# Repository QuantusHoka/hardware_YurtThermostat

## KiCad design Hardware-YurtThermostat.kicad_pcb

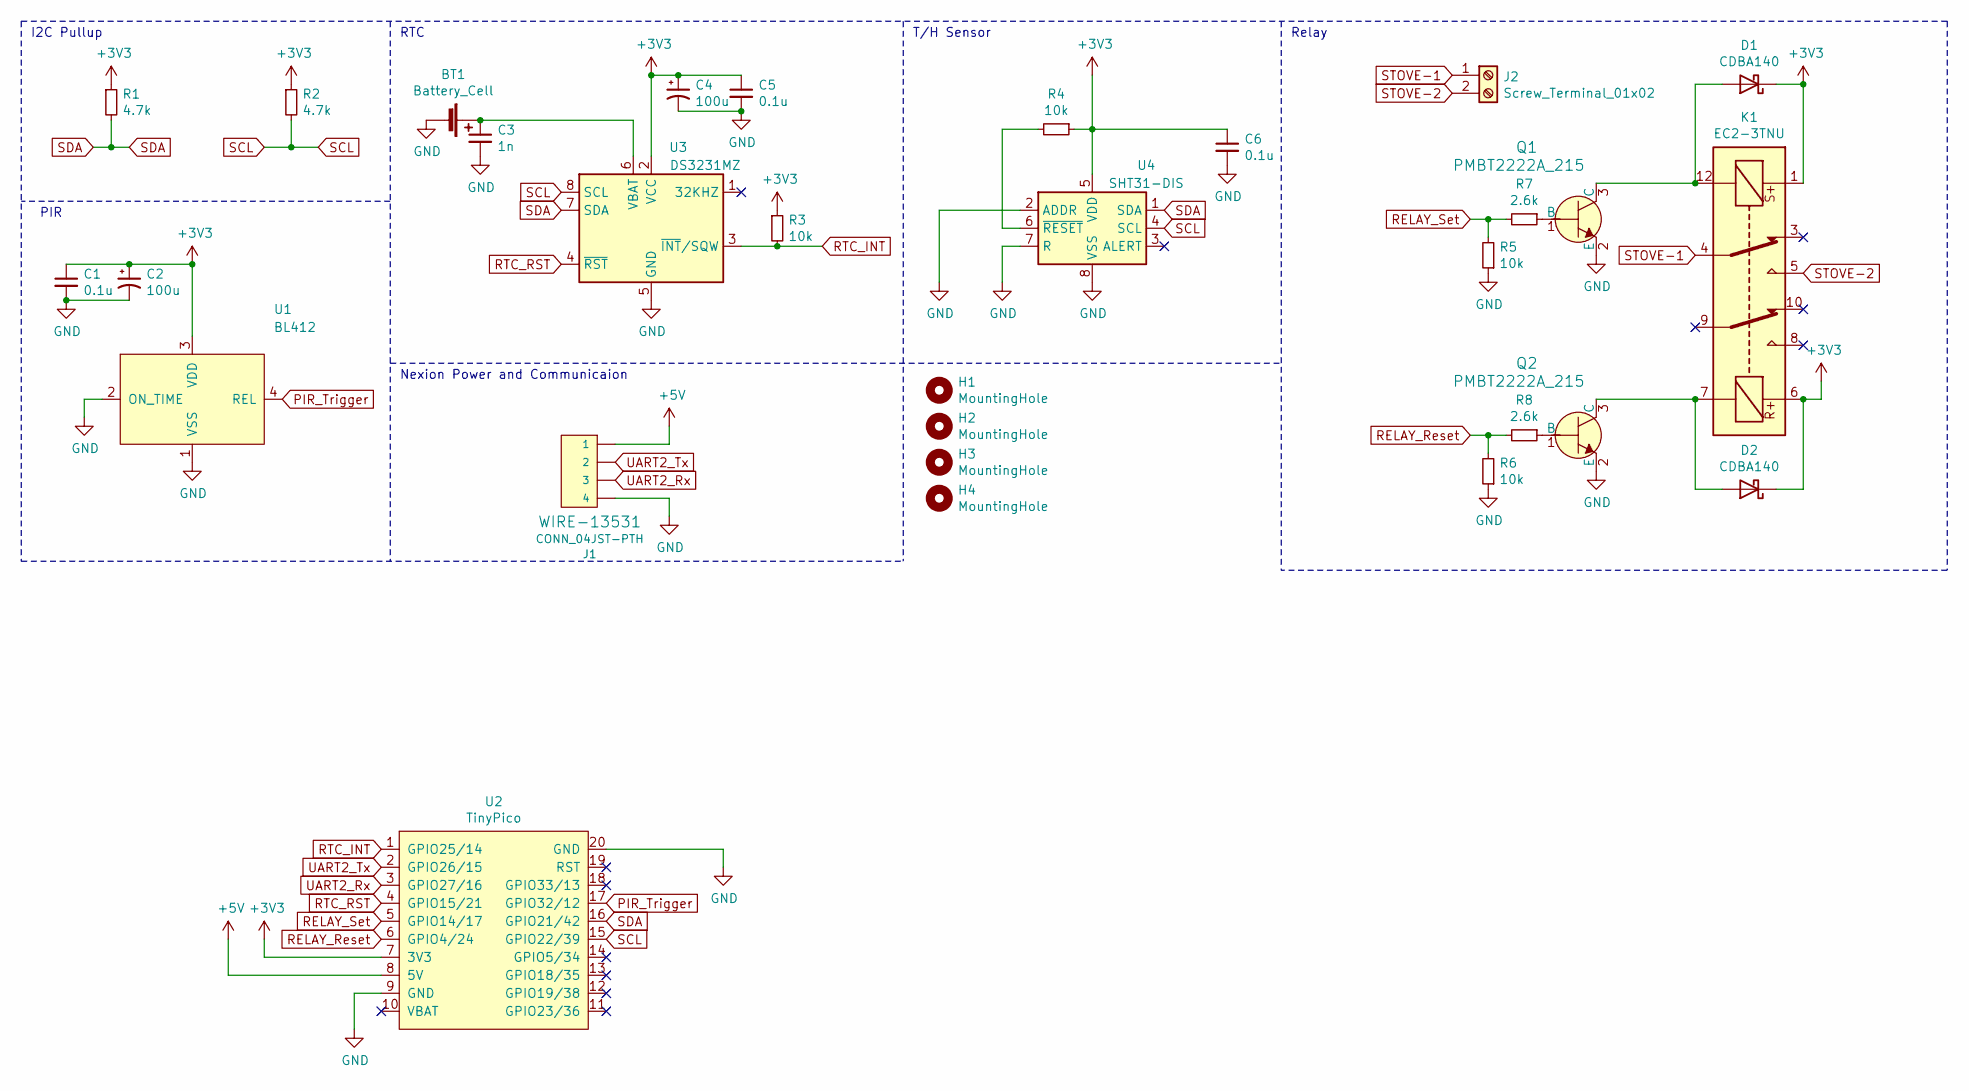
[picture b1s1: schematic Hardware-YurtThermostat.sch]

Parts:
BT1: Battery_Cell; BatteryHolder_Keystone_1060_1x2032
C1, C5, C6: 0.1u; C_0805_2012Metric_Pad1.18x1.45mm_HandSolder
C2, C4: 100u; CP_Elec_5x5.4
C3: 1n; C_0805_2012Metric_Pad1.18x1.45mm_HandSolder
D1, D2: CDBA140; D_SMA
H1, H2, H3, H4: MountingHole; MountingHole_3mm_Pad_TopBottom
J1: CONN_04JST-PTH; JST-4-PTH
J2: Screw_Terminal_01x02; Term_Block_1x2_P5mm
K1: EC2-3TNU; Relay_DPDT_Kemet_EC2_DoubleCoil
Q1, Q2: PMBT2222A_215; SOT-23-3; MPN PMBT2222A,215; Digi-Key_PN 1727-2956-1-ND
R1, R2: 4.7k; R_0805_2012Metric_Pad1.20x1.40mm_HandSolder
R3, R4, R5, R6: 10k; R_0805_2012Metric_Pad1.20x1.40mm_HandSolder
R7, R8: 2.6k; R_0805_2012Metric_Pad1.20x1.40mm_HandSolder
U1: BL412
U2: TinyPico
U3: DS3231MZ; SOIC-8_3.9x4.9mm_P1.27mm
U4: SHT31-DIS; Sensirion_DFN-8-1EP_2.5x2.5mm_P0.5mm_EP1.1x1.7mm

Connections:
+3V3: C1.1, C2.1, C4.1, C5.1, C6.1, D1.1 (K), D2.1 (K), K1.1, K1.6, R1.1, R2.1, R3.1, R4.1, U1.3 (VDD), U2.7 (3V3), U3.2 (VCC), U4.5 (VDD)
+5V: J1.1, U2.8 (5V)
GND: BT1.2 (-), C1.2, C2.2, C3.2, C4.2, C5.2, C6.2, J1.4, Q1.2 (E), Q2.2 (E), R5.1, R6.1, U1.1 (VSS), U1.2 (ON_TIME), U2.9 (GND), U2.20 (GND), U3.5 (GND), U4.2 (ADDR), U4.7 (R), U4.8 (VSS), U4.9 (VSS)
unnamed: BT1.1 (+), C3.1, U3.6 (VBAT)
unnamed: D1.2 (A), K1.12, Q1.3 (C)
unnamed: D2.2 (A), K1.7, Q2.3 (C)
unnamed: Q1.1 (B), R7.1
unnamed: Q2.1 (B), R8.1
unnamed: R4.2, U4.6 (~RESET)
PIR_Trigger: U1.4 (REL), U2.17 (GPIO32/12)
RELAY_Reset: R6.2, R8.2, U2.6 (GPIO4/24)
RELAY_Set: R5.2, R7.2, U2.5 (GPIO14/17)
RTC_INT: R3.2, U2.1 (GPIO25/14), U3.3 (~INT~/SQW)
RTC_RST: U2.4 (GPIO15/21), U3.4 (~RST)
SCL: R2.2, U2.15 (GPIO22/39), U3.8 (SCL), U4.4 (SCL)
SDA: R1.2, U2.16 (GPIO21/42), U3.7 (SDA), U4.1 (SDA)
STOVE-1: J2.1, K1.4
STOVE-2: J2.2, K1.5
UART2_Rx: J1.3, U2.3 (GPIO27/16)
UART2_Tx: J1.2, U2.2 (GPIO26/15)

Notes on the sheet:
I2C Pullup
PIR
RTC
Nexion Power and Communicaion
T/H Sensor
Relay

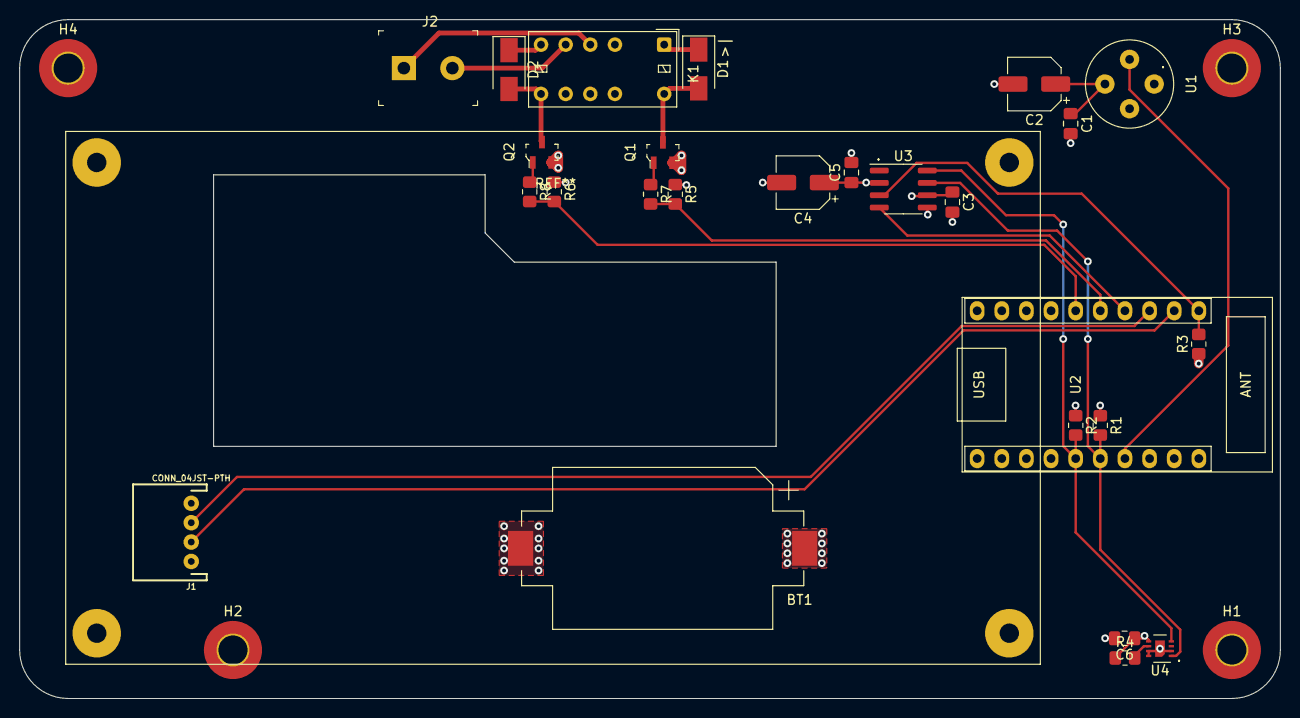
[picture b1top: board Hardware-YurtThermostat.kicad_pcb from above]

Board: 4 copper layers, 130.0 x 70.0 mm, 30 parts (0 on the bottom side), 20 nets.
